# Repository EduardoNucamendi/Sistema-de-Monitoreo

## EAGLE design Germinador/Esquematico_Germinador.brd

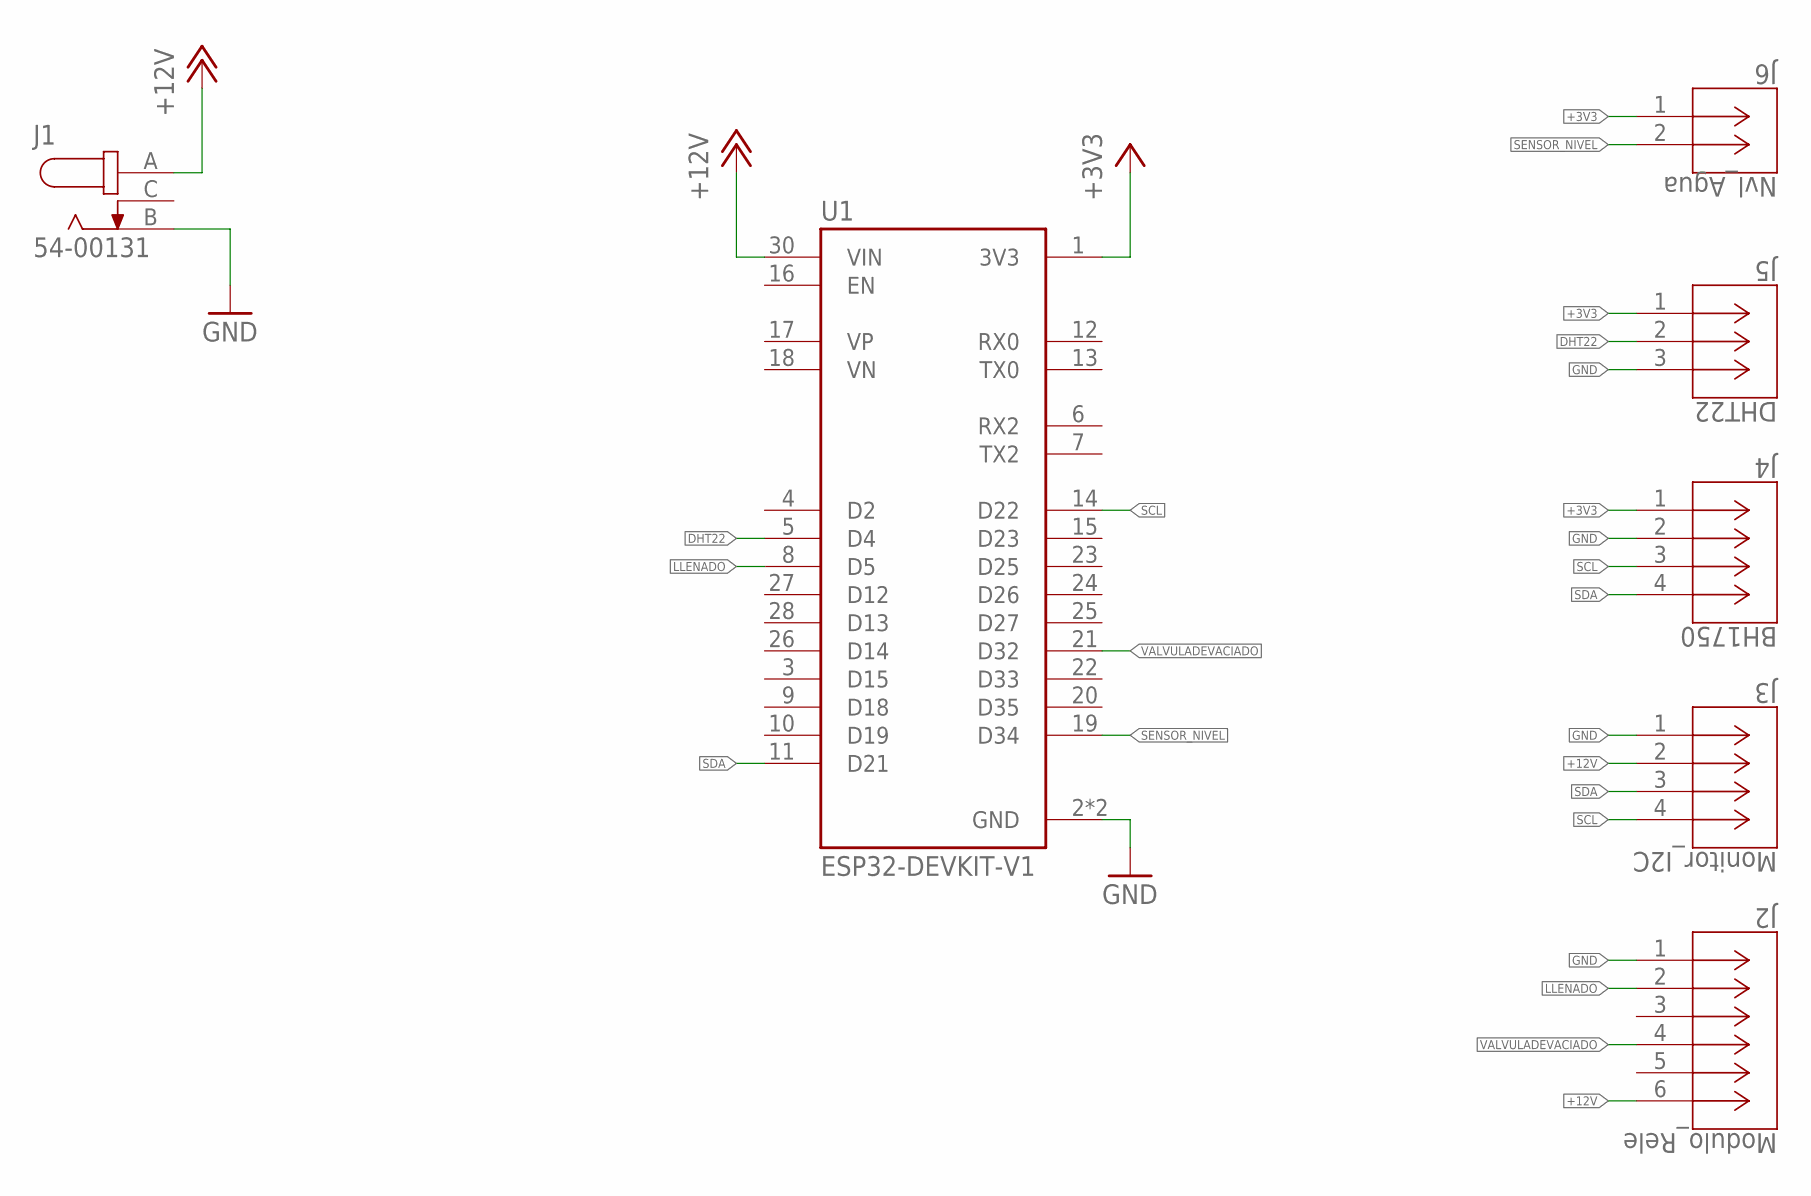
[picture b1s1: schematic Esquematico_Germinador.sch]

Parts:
J1: 54-00131
J2: Modulo_Rele; CONN_B6B-XH-A(LF)(SN)_JST
J3: Monitor_I2C; CONN_B4B-XH-A_(LF)(SN)_JST
J4: BH1750; CONN_B4B-XH-A_(LF)(SN)_JST
J5: DHT22; CONN_B3B-XH-A_JST
J6: Nvl_Agua; CONN_B2B-XH-A(LF)(SN)_JST
U1: ESP32-DEVKIT-V1; MODULE_ESP32_DEVKIT_V1

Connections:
+3V3: J4.1, J5.1, J6.1, U1.1 (3V3)
+12V: J1.A, J2.6, J3.2, U1.30 (VIN)
DHT22: J5.2, U1.5 (D4)
GND: J1.B, J2.1, J3.1, J4.2, J5.3, U1.2 (GND), U1.29 (GND)
LLENADO: J2.2, U1.8 (D5)
SCL: J3.4, J4.3, U1.14 (D22)
SDA: J3.3, J4.4, U1.11 (D21)
SENSOR_NIVEL: J6.2, U1.19 (D34)
VALVULADEVACIADO: J2.4, U1.21 (D32)

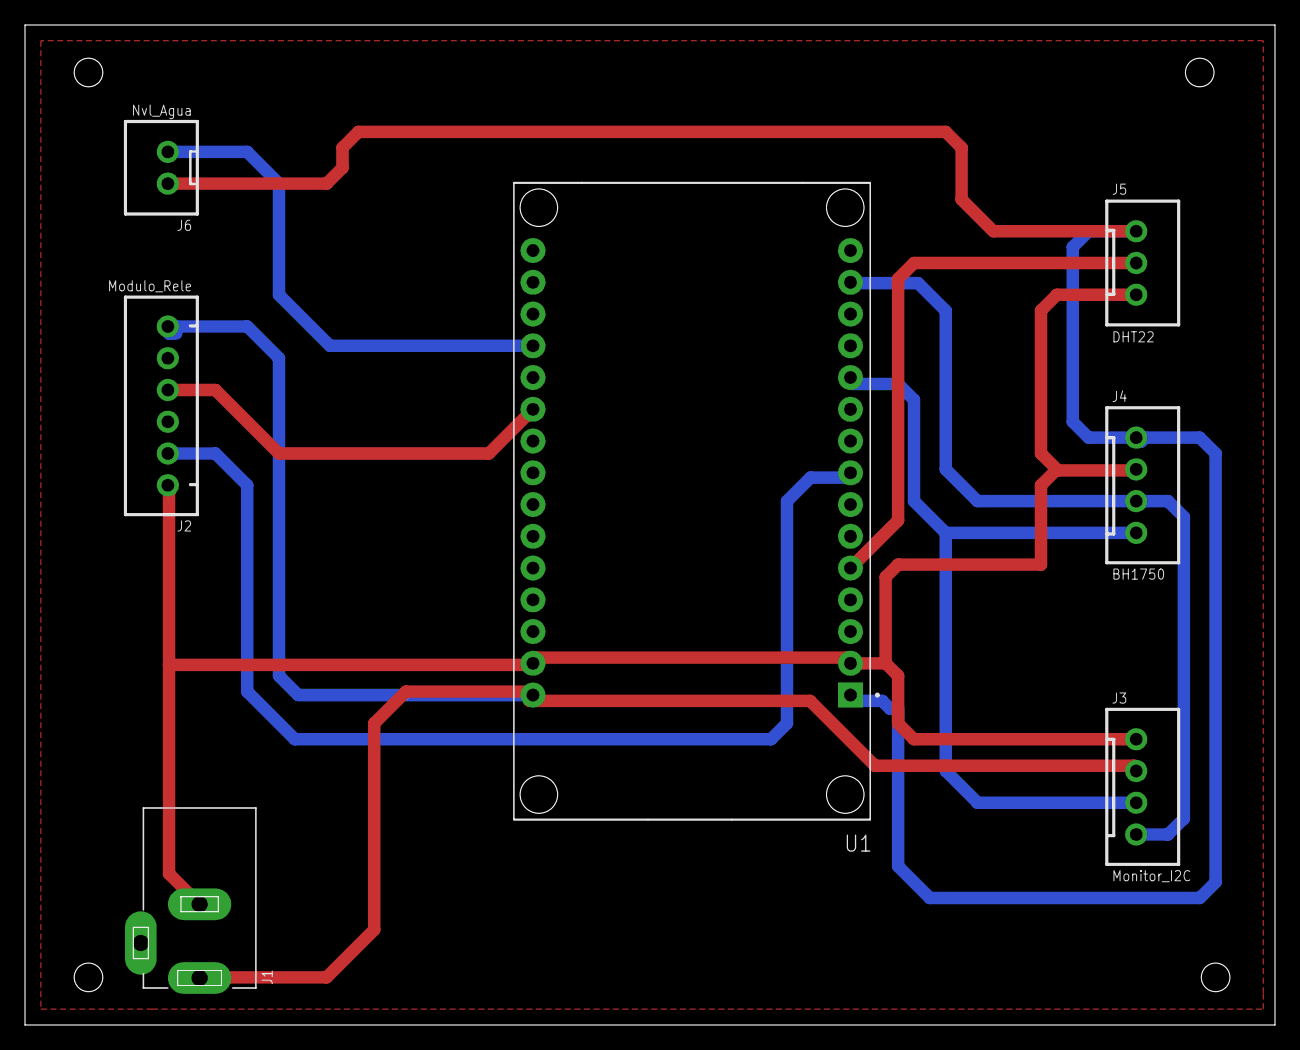
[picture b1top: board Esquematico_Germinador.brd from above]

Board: 2 copper layers, 100.0 x 80.0 mm, 7 parts (0 on the bottom side), 9 nets.

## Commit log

2024-11-13 Version 1 de la pagina web
2024-11-13 Version 1 pagina Web
2024-11-14 PCB design
2024-11-15 Archivos INO Deshidratador y Germinador
2024-11-15 Formato Gerber para fabricar la pcb
2024-11-21 Deshidratador_
2024-11-21 Germinador_Rutina

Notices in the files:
parts and their libraries:
COPYRIGHT: Copyright (C) 2018 Accelerated Designs. All rights reserved
